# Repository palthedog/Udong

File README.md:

# Udong
Udong is an open-source/open-hardware fighting game controller which supports rapid-trigger.

# How-Tos
## Firmware development
### Requirements
- PlatformIO w/ RP2040 support

TODO: Write more detailed document

## Update WebConf on github.io
`ng build --base-href=/Udong/`

`ng build --configuration=mock --base-href=/Udong/`

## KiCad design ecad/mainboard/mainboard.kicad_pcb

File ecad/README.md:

- Setup Kicad

-- Libraries
Install libraries below
-- Keyswitch Kicad Library
can be installed via "Plugin-Content manager" -> Library

-- 3D models
Configure Kicad path so that Kicad can find 3D models saved in our project dir.
In the project's main menu, click "Setting" -> "Configure Paths"
Then, add a new path and
Set Name to `UDONG_DIR` and Path to `(path-to-your-working-directory)/Udong/ecad`

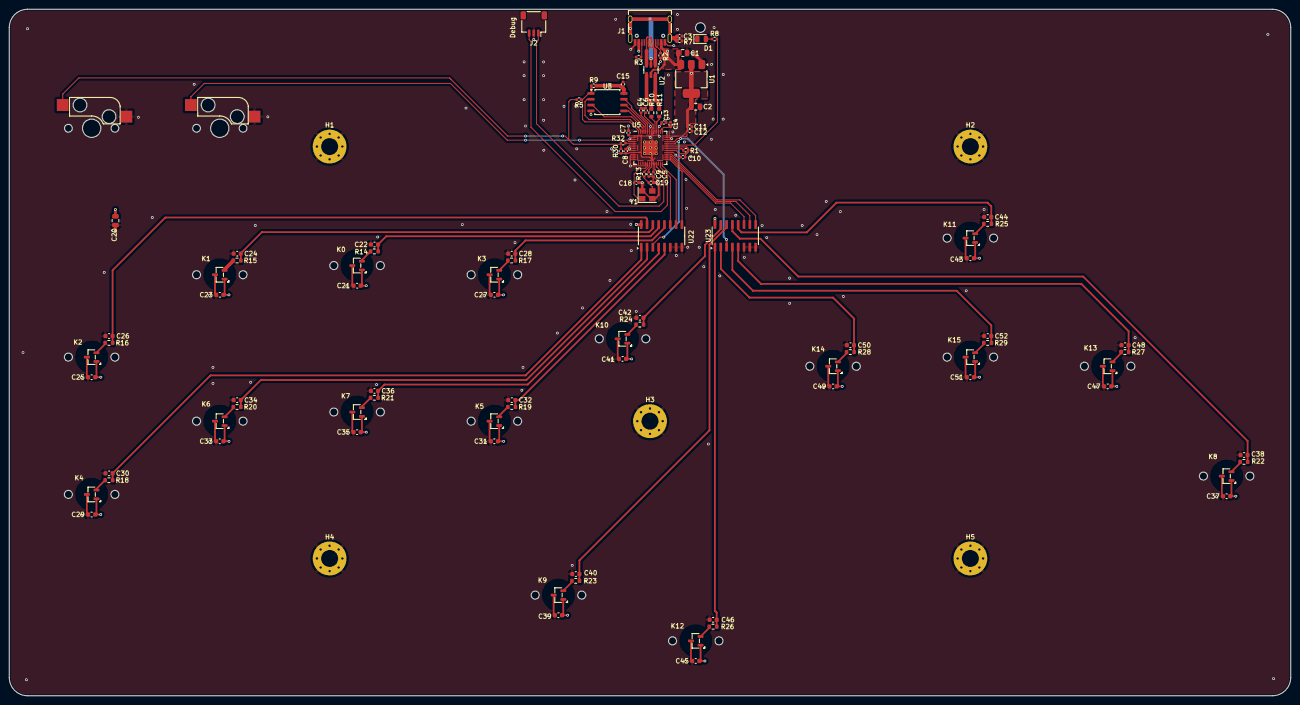
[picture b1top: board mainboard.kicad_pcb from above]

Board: 4 copper layers, 280.0 x 150.0 mm, 111 parts (0 on the bottom side), 70 nets.

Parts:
C1, C2, C20: 10u; C_0805_2012Metric
C3: 4.7nF; C_0402_1005Metric
C4, C5, C6, C7, C8, C9, C10, C11, C12, C15: 100n; C_0402_1005Metric
C13, C14: 1uF; C_0402_1005Metric
C18, C19: 15p; C_0402_1005Metric
C21, C22, C23, C24, C25, C26, C27, C28, C29, C30, C31, C32, C33, C34, C35, C36, C37, C38, C39, C40, C41, C42, C43, C44, C45, C46, C47, C48, C49, C50, C51, C52: 1uF; C_0603_1608Metric
D1: LED; LED_0805_2012Metric
H1, H2, H3, H4, H5: MountingHole_Pad; MountingHole_3.7mm_Pad_Via
J1: TYPE-C-31-M-12; USB_C_Receptacle_HRO_TYPE-C-31-M-12
J2: SWD; JST_SH_SM03B-SRSS-TB_1x03-1MP_P1.00mm_Horizontal
K0, K1, K2, K3, K4, K5, K6, K7, K8, K9, K10, K11, K12, K13, K14, K15: DRV5056A3xQDBZxR; SK20_hall_IC
R1, R9, R30: 10k; R_0402_1005Metric
R2, R3: 5.1k; R_0402_1005Metric
R5, R13, R32: 1k; R_0402_1005Metric
R7: 1M; R_0402_1005Metric
R8: 470; R_0402_1005Metric
R10, R11: 27; R_0603_1608Metric
R14, R15, R16, R17, R18, R19, R20, R21, R22, R23, R24, R25, R26, R27, R28, R29: 100; R_0603_1608Metric
SW3, SW4: SW_Push; MX_Socket
U1: NCP1117ST33T3G; SOT-223-3_TabPin2
U2: USBLC6-2SC6; SOT-23-6
U3: W25Q128JVS; SOIC-8_5.23x5.23mm_P1.27mm
U5: RP2040; RP2040-QFN-56
U22, U23: CD4051BM96; SOIC-16_3.9x9.9mm_P1.27mm
Y1: ABM8-272-T3; Crystal_SMD_3225-4Pin_3.2x2.5mm

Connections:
+1V1: C4.1, C5.1, C13.1, U5.23 (DVDD), U5.45 (VREG_VOUT), U5.50 (DVDD)
+3.3V: C2.1, C6.1, C7.1, C8.1, C9.1, C10.1, C11.1, C12.1, C14.1, C15.1, C20.1, C21.2, C23.2, C25.2, C27.2, C29.2, C31.2, C33.2, C35.2, C37.2, C39.2, C41.2, C43.2, C45.2, C47.2, C49.2, C51.2, K0.1 (VCC), K1.1 (VCC), K2.1 (VCC), K3.1 (VCC), K4.1 (VCC), K5.1 (VCC), K6.1 (VCC), K7.1 (VCC), K8.1 (VCC), K9.1 (VCC), K10.1 (VCC), K11.1 (VCC), K12.1 (VCC), K13.1 (VCC), K14.1 (VCC), K15.1 (VCC), R9.1, R30.1, U1.2 (VO), U3.8 (VCC), U5.1 (IOVDD), U5.10 (IOVDD), U5.22 (IOVDD), U5.33 (IOVDD), U5.42 (IOVDD), U5.43 (ADC_AVDD), U5.44 (VREG_IN), U5.48 (USB_VDD), U5.49 (IOVDD), U22.16 (VDD), U23.16 (VDD)
/D+: J1.A6 (D+), J1.B6 (D+), U2.3 (I/O2)
/D-: J1.A7 (D-), J1.B7 (D-), U2.1 (I/O1)
AS0: C22.2, R14.2, U22.13 (X0)
AS1: C24.2, R15.2, U22.14 (X1)
AS2: C26.2, R16.2, U22.15 (X2)
AS3: C28.2, R17.2, U22.12 (X3)
AS4: C30.2, R18.2, U22.1 (X4)
AS5: C32.2, R19.2, U22.5 (X5)
AS6: C34.2, R20.2, U22.2 (X6)
AS7: C36.2, R21.2, U22.4 (X7)
AS8: C38.2, R22.2, U23.13 (X0)
AS9: C40.2, R23.2, U23.14 (X1)
AS10: C42.2, R24.2, U23.15 (X2)
AS11: C44.2, R25.2, U23.12 (X3)
AS12: C46.2, R26.2, U23.1 (X4)
AS13: C48.2, R27.2, U23.5 (X5)
AS14: C50.2, R28.2, U23.2 (X6)
AS15: C52.2, R29.2, U23.4 (X7)
BOOTSEL_SW: R5.2, R30.2, R32.2, SW4.1
DS_0_IN: SW3.1, U5.4 (GPIO2)
DS_1_IN: R32.1, U5.5 (GPIO3)
GND: C1.2, C2.2, C3.2, C4.2, C5.2, C6.2, C7.2, C8.2, C9.2, C10.2, C11.2, C12.2, C13.2, C14.2, C15.2, C18.2, C19.2, C20.2, C21.1, C22.1, C23.1, C24.1, C25.1, C26.1, C27.1, C28.1, C29.1, C30.1, C31.1, C32.1, C33.1, C34.1, C35.1, C36.1, C37.1, C38.1, C39.1, C40.1, C41.1, C42.1, C43.1, C44.1, C45.1, C46.1, C47.1, C48.1, C49.1, C50.1, C51.1, C52.1, D1.1 (K), H1.1, H2.1, H3.1, H4.1, H5.1, J1.A1 (GND), J1.A12 (GND), J1.B1 (GND), J1.B12 (GND), J2.2, K0.3 (GND), K1.3 (GND), K2.3 (GND), K3.3 (GND), K4.3 (GND), K5.3 (GND), K6.3 (GND), K7.3 (GND), K8.3 (GND), K9.3 (GND), K10.3 (GND), K11.3 (GND), K12.3 (GND), K13.3 (GND), K14.3 (GND), K15.3 (GND), R1.2, R2.2, R3.1, R7.2, SW3.2, SW4.2, U1.1 (GND), U3.4 (GND), U5.2 (GPIO0), U5.3 (GPIO1), U5.6 (GPIO4), U5.7 (GPIO5), U5.8 (GPIO6), U5.9 (GPIO7), U5.11 (GPIO8), U5.12 (GPIO9), U5.13 (GPIO10), U5.14 (GPIO11), U5.15 (GPIO12), U5.16 (GPIO13), U5.17 (GPIO14), U5.18 (GPIO15), U5.19 (TESTEN), U5.34 (GPIO22), U5.36 (GPIO24), U5.40 (GPIO28_ADC2), U5.41 (GPIO29_ADC3), U5.57 (GND), U22.6 (INH), U22.7 (VEE), U22.8 (VSS), U23.6 (INH), U23.7 (VEE), U23.8 (VSS), Y1.2, Y1.4
GPIO25: R8.2, U5.37 (GPIO25)
MUX0_A: U5.27 (GPIO16), U22.11 (A)
MUX0_B: U5.28 (GPIO17), U22.10 (B)
MUX0_C: U5.29 (GPIO18), U22.9 (C)
MUX0_OUT: U5.38 (GPIO26_ADC0), U22.3 (X)
MUX1_A: U5.30 (GPIO19), U23.11 (A)
MUX1_B: U5.31 (GPIO20), U23.10 (B)
MUX1_C: U5.32 (GPIO21), U23.9 (C)
MUX1_OUT: U5.39 (GPIO27_ADC1), U23.3 (X)
unnamed: C19.1, R13.2, Y1.3
unnamed: D1.2 (A), R8.1
unnamed: J1.A5 (CC1), R2.1
unnamed: J1.B5 (CC2), R3.2
unnamed: K0.2 (OUT), R14.1
unnamed: K1.2 (OUT), R15.1
unnamed: K2.2 (OUT), R16.1
unnamed: K3.2 (OUT), R17.1
unnamed: K4.2 (OUT), R18.1
unnamed: K5.2 (OUT), R19.1
unnamed: K6.2 (OUT), R20.1
unnamed: K7.2 (OUT), R21.1
unnamed: K8.2 (OUT), R22.1
unnamed: K9.2 (OUT), R23.1
unnamed: K10.2 (OUT), R24.1
unnamed: K11.2 (OUT), R25.1
unnamed: K12.2 (OUT), R26.1
unnamed: K13.2 (OUT), R27.1
unnamed: K14.2 (OUT), R28.1
unnamed: K15.2 (OUT), R29.1
unnamed: R1.1, U5.35 (GPIO23)
unnamed: R11.2, U5.46 (USB_DM)
unnamed: R10.2, U5.47 (USB_DP)
QSPI_SCLK: U3.6 (CLK), U5.52 (QSPI_SCLK)
QSPI_SD0: U3.5 (DI(IO0)), U5.53 (QSPI_SD0)
QSPI_SD1: U3.2 (DO(IO1)), U5.55 (QSPI_SD1)
QSPI_SD2: U3.3 (IO2), U5.54 (QSPI_SD2)
QSPI_SD3: U3.7 (IO3), U5.51 (QSPI_SD3)
QSPI_SS: R5.1, R9.2, U3.1 (~CS), U5.56 (QSPI_SS)
SHIELD: C3.1, J1.S1 (SHIELD), R7.1, U2.2 (GND)
SWCLK: J2.1, U5.24 (SWCLK)
SWD: J2.3, U5.25 (SWD)
USB_D+: R10.1, U2.4 (I/O2)
USB_D-: R11.1, U2.6 (I/O1)
VBUS: C1.1, J1.A4 (VBUS), J1.A9 (VBUS), J1.B4 (VBUS), J1.B9 (VBUS), U1.3 (VI), U2.5 (VBUS)
XIN: C18.1, U5.20 (XIN), Y1.1
XOUT: R13.1, U5.21 (XOUT)

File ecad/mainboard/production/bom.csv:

Designator,Footprint,Quantity,Value,LCSC Part #
"C1, C2, C20",0805,3,10u,
"C10, C11, C12, C15, C4, C5, C6, C7, C8, C9",0402,10,100n,
"C13, C14",0402,2,1uF,
"C18, C19",0402,2,15p,
"C21, C22, C23, C24, C25, C26, C27, C28, C29, C30, C31, C32, C33, C34, C35, C36, C37, C38, C39, C40, C41, C42, C43, C44, C45, C46, C47, C48, C49, C50, C51, C52",0603,32,1uF,
C3,0402,1,4.7nF,
D1,0805,1,LED,C2297
J1,USB_C_Receptacle_HRO_TYPE-C-31-M-12,1,TYPE-C-31-M-12,C165948
J2,JST_SH_SM03B-SRSS-TB_1x03-1MP_P1.00mm_Horizontal,1,SWD,C160403
"K0, K1, K10, K11, K12, K13, K14, K15, K2, K3, K4, K5, K6, K7, K8, K9",SK20_hall_IC,16,DRV5056A3xQDBZxR,C2866615
"R1, R30, R9",0402,3,10k,
"R10, R11",0603,2,27,
"R13, R32, R5",0402,3,1k,
"R14, R15, R16, R17, R18, R19, R20, R21, R22, R23, R24, R25, R26, R27, R28, R29",0603,16,100,
"R2, R3",0402,2,5.1k,
R7,0402,1,1M,
R8,0402,1,470,
"SW3, SW4",MX_Socket,2,SW_Push,C5156480
U1,SOT-223-3_TabPin2,1,NCP1117ST33T3G,C26537
U2,SOT-23-6,1,USBLC6-2SC6,C2827654
"U22, U23",SOIC-16_3.9x9.9mm_P1.27mm,2,CD4051BM96,C21379
U3,SOIC-8_5.23x5.23mm_P1.27mm,1,W25Q128JVS,
U5,RP2040-QFN-56,1,RP2040,
Y1,Crystal_SMD_3225-4Pin_3.2x2.5mm,1,ABM8-272-T3,

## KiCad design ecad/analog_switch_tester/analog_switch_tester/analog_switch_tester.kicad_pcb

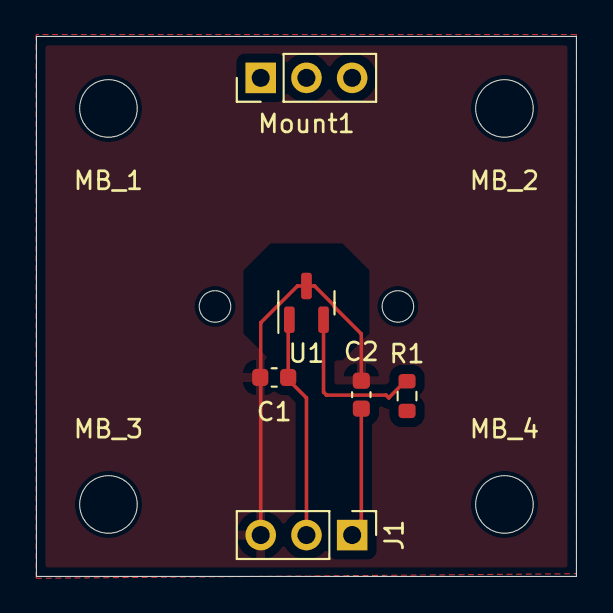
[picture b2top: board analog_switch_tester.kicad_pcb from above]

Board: 2 copper layers, 30.0 x 30.0 mm, 10 parts (0 on the bottom side), 4 nets.

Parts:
C1, C2: 1uF; C_0603_1608Metric
J1: Conn_01x03_Pin; PinHeader_1x03_P2.54mm_Vertical
MB_1, MB_2, MB_3, MB_4: MountingHole_3.2mm_M3
Mount1: Conn_01x03_Pin; PinHeader_1x03_P2.54mm_Vertical
R1: 100; R_0603_1608Metric
U1: DRV5056A1xQDBZxR; SW_Cherry_MX_PCB_1.00u_hall_effect

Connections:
GNDA: C1.1, C2.1, J1.3, U1.3 (GND)
unnamed: R1.1, U1.2 (OUT)
OUT: C2.2, J1.1, R1.2
V_AREF: C1.2, J1.2, U1.1 (VCC)

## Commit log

2024-06-02 add led.h
2024-06-02 simplify HID descriptor
2024-06-02 move led.h into io_utils/
2024-06-04 abstract input/output
2024-06-04 implement Multiplexer
2024-06-04 debug in/out for analog switches
2024-06-05 mv firmware codes into firmware/
2024-06-05 very initial kicad project for analog switch tester
2024-06-05 Add low-pass filters
2024-06-06 measure
2024-06-06 plot gerber files
2024-06-06 calibrator
2024-06-06 fix units
2024-06-06 add solver
2024-06-07 Measure a pressed depth from a measured magnetic flux. - Calibrate/Solve Br(remenance) from Br_near, Br_far, KeyStroke(4mm) - Create a look-up table from magnetic-flux to pressed depth
2024-06-07 Connect hall-ICs to AnalogSwitch class
2024-06-07 add more debug logs
2024-06-09 add noise filter
2024-06-09 Calibrate zero point
2024-06-09 remove all warnings
2024-06-09 save/load calibration data on to the file system.
2024-06-09 debug log. TODO: Save only when the game pad is in idle mode
2024-06-10 cleanup
2024-06-10 throttling
2024-06-10 linear interpolation
2024-06-10 reset command
2024-06-10 set VID/PID
2024-06-11 use custom tusb_config.h
2024-06-11 rename NoiseFilter to MultiSampling
2024-06-11 Implement rapid trigger
2024-06-11 Disable multi sampling
2024-06-13 Initial changes for web based configuratin tool (static site generation)
2024-06-13 change color
2024-06-14 update config on the root component
2024-06-14 Intial changes for supporting switch grouping
2024-06-14 make selected group editable (only on UI. not saved yet)
2024-06-14 add a toggle button to switch rapid/static trigger mode
2024-06-14 switch configurator even when the user select same group
2024-06-14 minor refactoring
2024-06-14 construct Circuit from UdonConfig
2024-06-14 use smart pointer almost everywhere
2024-06-14 save user configuration files
2024-06-15 test github pages
2024-06-15 8 buttons yay!
2024-06-16 comments out debug codes
2024-06-16 kicad
2024-06-16 place parts except analog switches
2024-06-16 place all parts
2024-06-16 replace some parts. Just BEFORE running autoroute
2024-06-17 fix all DRC errors for connected parts
2024-06-17 refactor some patterns
2024-06-17 Udong board rev.1
2024-06-17 add new footprints but broken pcb
2024-06-17 rev1.1
2024-06-18 Made a top-plate for Udong Mainboard
2024-06-18 remove keyboard_footprint
2024-06-19 add 3d model for type-c socket
2024-06-19 WIP: PCB case
2024-06-19 case
2024-06-19 bottom case
2024-06-20 ceil
2024-06-20 Very initial housing data.
2024-06-20 Put labels about button assignment on User.comments layer
2024-06-21 prepare for the rev.1 board
2024-06-24 fix: init Serial before use
2024-06-24 WIP: mock serial service
2024-06-24 MockSerialService
2024-06-24 render buttons with SVG
2024-06-24 Show button name
2024-06-24 WebConf: Support changing button assignments
2024-06-24 Add AppConsts
2024-06-24 Support running the server with mocked Udong device
2024-06-24 Firmware records button assigmnent
2024-06-24 Firmware: button assignment
2024-06-24 ButtonId supports d-pad now
2024-06-24 Update docs
2024-06-24 Update docs again
2024-06-24 Update docs again and again
2024-06-24 mock prod
2024-06-25 Update packages
2024-06-25 Fix bugs in convertFromJson
2024-06-25 add logger
2024-06-25 Extract gamepad report logic into other classes to support D-pad in the following changes
2024-06-25 Supports D-pad
2024-06-26 Clean up
2024-06-26 WIP: Replacing hand written config structure with protobuf. We got rid of hand written config.ts now. Next task is to do similar job for firmware!
2024-06-26 Sample proto file
2024-06-26 Update modules
2024-06-26 save/load firmware config in protobuf wire format
2024-06-26 FW supports Binary fire format
2024-06-26 Remove unused code; hand written config structures
2024-06-26 ahh forgot to add UNSPECIFIED values on proto enum
2024-06-26 fix warning
2024-07-01 delay 1 micro second for waiting the Multiplexer to finish switching the output/input
2024-07-02 Fix a bug; press left then right lacks `break`
2024-07-04 switch from nanopb to decaproto
2024-07-04 Loading/Sending proto; remaining task is to load config
2024-07-04 Save config w/ decaproto
2024-07-05 Support Digital Switch
2024-07-05 Update proto definitions (not compatible...)
2024-07-05 Update default config
2024-07-05 Remove a libarary
2024-07-06 Configure platformio to use Debug Probe
2024-07-07 Update circuit for the new design
2024-07-07 Update PCB. Next task would be move switch positions
2024-07-07 Now, Webconf is the root source of switchs coordinates
2024-07-07 New button coordinates
2024-07-08 Make a DigitalSwitch field so that scripts can configure digital-switch related parts easily
2024-07-08 Python script to update switch positions
2024-07-08 Place all buttons
2024-07-11 rev2 board
2024-07-11 Board config
2024-07-11 Separate board specific code and shared code
2024-07-11 Stop saving calibration data. Instead, just initialize the table with a range data with much margin
2024-07-12 Put readonly board_name.txt on LittleFS filesystem so that our firmware can distinguish board type at runtime without using different firmwares for different boards
2024-07-14 Temporal work around for a dead-lock issue: https://github.com/adafruit/Adafruit_TinyUSB_Arduino/issues/238
2024-07-14 communicate with the board realtime
2024-07-14 Implements an RPC to print an analog switch state on Web Configulator.
2024-07-15 WebConf: Serial Service has its own locking system for Serial writer.
    It enables us to `await` the writer to be released when it's locked by other routine.
2024-07-15 Add Board definition for prototype2
2024-07-15 Remove Trigger::ToConfig
2024-07-15 WebConf renders more info
2024-07-15 WebConf: Select the 1st analog button by default
2024-07-15 Firmware: Print a log when detect a low polling rate.
    As far as I checked, it happens only when the firmware encodes proto message.
2024-07-15 WebConf: Show only important info on the graph
    For example, hide the actuation point while the switch is triggered
2024-07-16 Firmware: Remove a unused function.
2024-07-16 WebConf: Clear obsolte data
    Clear obsolte data when:
    - Serial port is disconnected
    - Select a different switch
2024-07-17 WebConf: Fix layout
2024-07-17 WebConf: Mouse wheel for zooming in/out the preview graph
2024-07-17 WebConf: Tooltip shows formated timestamp
2024-07-17 Add a unit test
2024-07-17 WebConf: One more digit
2024-07-17 Firmaware: Move generated proto files under lib/ so that unit tests can refer them
2024-07-17 Update decaproto
2024-07-17 Add some logging
2024-07-17 Put a tiny USB library with a workaround in lib/
2024-07-17 Change timeout duration from 10ms to 1ms.
2024-07-18 Disable USBCTRL_IRQ while sending HID report for preventing deadlock
2024-07-18 teleplot does not need delay now
2024-07-21 Firmware supports to configure total-travel-distance
2024-07-23 WEB_CONF: Adds a slider to configure total travel distance
2024-07-23 Firmware: Lookup table reflects max_travel_distance now
2024-07-24 Add basic tests for ComplementMessage function
2024-07-24 Adds a new case CAD which has minor fixes from rev2
    1. rev2 had a bad gap between topplate and pcb board.
    2. Closes a hole for the debug port (it's pretty difficult to insert the cable through the hole)
    3. Add rounded edge to support the pcb board so that we can keep the distance between pcb and the switch as close as we can.
2024-07-24 WebConf: fix mock
2024-07-24 WebConf: Supports SOCD mode
2024-07-24 WebConf: Hides SOCD mode config if the firmware does not support it
2024-07-24 Firmware: Supports SOCD Cleaner
2024-09-12 Hardware version 1.0
2026-01-08 Temporal fix: increase budget
2026-01-08 Update docs/
